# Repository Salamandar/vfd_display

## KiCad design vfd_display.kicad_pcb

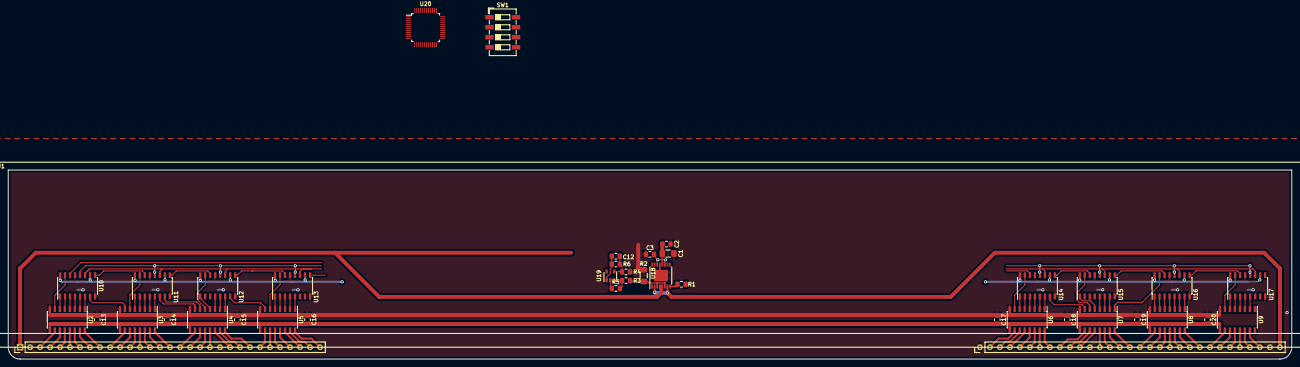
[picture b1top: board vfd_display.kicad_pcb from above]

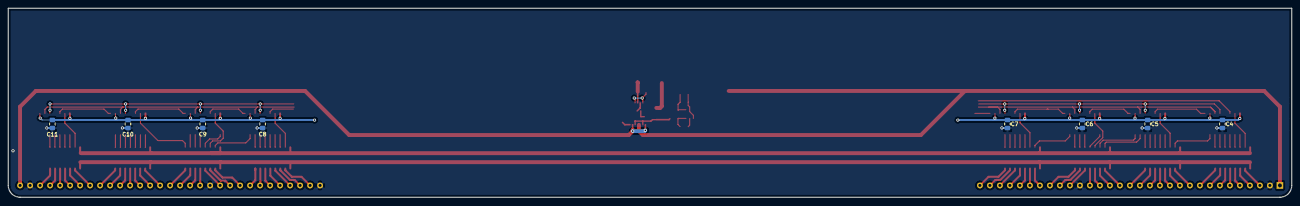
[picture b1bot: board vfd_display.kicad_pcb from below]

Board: 2 copper layers, 326.0 x 48.0 mm, 47 parts (8 on the bottom side), 132 nets.

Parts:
C1: 10u; C_1206_3216Metric_Pad1.42x1.75mm_HandSolder
C2, C4, C5, C6, C7, C8, C9, C10, C11, C13, C14, C15, C16, C17, C18, C19, C20: 100n; C_0805_2012Metric_Pad1.15x1.40mm_HandSolder
C3: 2.2u; C_0805_2012Metric_Pad1.15x1.40mm_HandSolder
C12: 33n; C_0805_2012Metric_Pad1.15x1.40mm_HandSolder
R1: 10k; R_0805_2012Metric_Pad1.15x1.40mm_HandSolder
R2: R_sense 500mW; R_1206_3216Metric_Pad1.42x1.75mm_HandSolder
R3, R4: 100; R_0805_2012Metric_Pad1.15x1.40mm_HandSolder
R5, R6: 47k; R_0805_2012Metric_Pad1.15x1.40mm_HandSolder
SW1: SW_DIP_x04; SW_DIP_SPSTx04_Slide_6.7x11.72mm_W6.73mm_P2.54mm_LowProfile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
U1: DC201LA
U2, U3, U4, U5, U6, U7, U8, U9: ULN2003; SOIC-16_3.9x9.9mm_P1.27mm
U10, U11, U12, U13, U14, U15, U16, U17: 74HC595; SOIC-16_3.9x9.9mm_P1.27mm
U18: DRV8848; TSSOP-16-1EP_4.4x5mm_P0.65mm
U19: TSZ121ILT; SOT-23-5
U20: STM32F302C8Tx; LQFP-48_7x7mm_P0.5mm

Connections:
+3V3: C4.1, C5.1, C6.1, C7.1, C8.1, C9.1, C10.1, C11.1, R1.2, U10.10, U10.16, U11.10, U11.16, U12.10, U12.16, U13.10, U13.16, U14.10, U14.16, U15.10, U15.16, U16.10, U16.16, U17.10, U17.16, U19.5, U20.9
/Filament_ADC: C12.1, R6.1, U19.1
/Filament_PWR: C1.2, C2.2, U18.12
/Grids_Anodes_Power: C13.2, C14.2, C15.2, C16.2, C17.2, C18.2, C19.2, C20.2, U2.9, U3.9, U4.9, U5.9, U6.9, U7.9, U8.9, U9.9
/VFD/Filament_In_A: U1.62, U18.2, U18.7
/VFD/Filament_In_B: U1.1, U18.4, U18.5
/VFD/G1: U7.5, U15.1
/VFD/G2: U7.6, U15.15
/VFD/G3: U7.7, U14.7
/VFD/G4: U6.1, U14.6
/VFD/G5: U6.2, U14.5
/VFD/G6: U6.3, U14.4
/VFD/G7: U6.4, U14.3
/VFD/G8: U6.5, U14.2
/VFD/G9: U6.6, U14.1
/VFD/G10: U6.7, U14.15
/VFD/G11: U5.1, U13.5
/VFD/G12: U5.2, U13.4
/VFD/G13: U5.3, U13.3
/VFD/G14: U5.4, U13.2
/VFD/G15: U5.5, U13.1
/VFD/G16: U5.6, U13.15
/VFD/G17: U5.7, U12.7
/VFD/G18: U4.1, U12.6
/VFD/G19: U4.2, U12.5
/VFD/G20: U4.3, U12.4
/VFD/P1: U2.7, U10.15
/VFD/P2: U2.6, U10.1
/VFD/P3: U2.5, U10.2
/VFD/P4: U2.4, U10.3
/VFD/P5: U2.3, U10.4
/VFD/P6: U2.2, U10.5
/VFD/P7: U2.1, U10.6
/VFD/P8: U3.7, U10.7
/VFD/P9: U3.6, U11.15
/VFD/P10: U3.5, U11.1
/VFD/P11: U3.4, U11.2
/VFD/P12: U3.3, U11.3
/VFD/P13: U3.2, U11.4
/VFD/P14: U3.1, U11.5
/VFD/P15: U4.7, U11.6
/VFD/P16: U4.6, U11.7
/VFD/P17: U4.5, U12.15
/VFD/P18: U4.4, U12.1
/VFD/P19: U9.2, U17.5
/VFD/P20: U9.3, U17.4
/VFD/P21: U9.4, U17.3
/VFD/P22: U9.5, U17.2
/VFD/P23: U9.6, U17.1
/VFD/P24: U9.7, U17.15
/VFD/P25: U8.1, U16.7
/VFD/P26: U8.2, U16.6
/VFD/P27: U8.3, U16.5
/VFD/P28: U8.4, U16.4
/VFD/P29: U8.5, U16.3
/VFD/P30: U8.6, U16.2
/VFD/P31: U8.7, U16.1
/VFD/P32: U7.1, U16.15
/VFD/P33: U7.2, U15.7
/VFD/P34: U7.3, U15.6
/VFD/P35: U7.4, U15.5
/VFD/RCLK1: U10.12, U11.12, U12.12, U13.12
/VFD/RCLK2: U14.12, U15.12, U16.12, U17.12
/VFD/SRCLK1: U10.11, U11.11, U12.11, U13.11
/VFD/SRCLK2: U14.11, U15.11, U16.11, U17.11
GND: C1.1, C2.1, C3.1, C4.2, C5.2, C6.2, C7.2, C8.2, C9.2, C10.2, C11.2, C13.1, C14.1, C15.1, C16.1, C17.1, C18.1, C19.1, C20.1, R2.2, R4.2, R5.1, SW1.5, SW1.6, SW1.7, SW1.8, U1.2, U1.21, U1.32, U1.43, U1.61, U2.8, U3.8, U4.8, U5.8, U6.8, U7.8, U8.8, U9.8, U10.8, U10.13, U11.8, U11.13, U12.8, U12.13, U13.8, U13.13, U14.8, U14.13, U15.8, U15.13, U16.8, U16.13, U17.8, U17.13, U18.13, U18.17, U19.2, U20.8, U20.23, U20.35, U20.47
unnamed: C3.2, U18.11, U18.14
unnamed: C12.2, R4.1, R6.2, U19.4
unnamed: R1.1, U18.8
unnamed: R2.1, R3.2, U18.3, U18.6
unnamed: R3.1, R5.2, U19.3
unnamed: U1.3, U2.10
unnamed: U1.4, U2.11
unnamed: U1.5, U2.12
unnamed: U1.6, U2.13
unnamed: U1.7, U2.14
unnamed: U1.8, U2.15
unnamed: U1.9, U2.16
unnamed: U1.10, U3.10
unnamed: U1.11, U3.11
unnamed: U1.12, U3.12
unnamed: U1.13, U3.13
unnamed: U1.14, U3.14
unnamed: U1.15, U3.15
unnamed: U1.16, U3.16
unnamed: U1.17, U4.10
unnamed: U1.18, U4.11
unnamed: U1.19, U4.12
unnamed: U1.20, U4.13
unnamed: U1.22, U4.14
unnamed: U1.23, U4.15
unnamed: U1.24, U4.16
unnamed: U1.25, U5.10
unnamed: U1.26, U5.11
unnamed: U1.27, U5.12
unnamed: U1.28, U5.13
unnamed: U1.29, U5.14
unnamed: U1.30, U5.15
unnamed: U1.31, U5.16
unnamed: U1.33, U6.10
unnamed: U1.34, U6.11
unnamed: U1.35, U6.12
unnamed: U1.36, U6.13
unnamed: U1.37, U6.14
unnamed: U1.38, U6.15
unnamed: U1.39, U6.16
unnamed: U1.40, U7.10
unnamed: U1.41, U7.11
unnamed: U1.42, U7.12
unnamed: U1.44, U7.13
unnamed: U1.45, U7.14
unnamed: U1.46, U7.15
unnamed: U1.47, U7.16
unnamed: U1.48, U8.10
unnamed: U1.49, U8.11
unnamed: U1.50, U8.12
unnamed: U1.51, U8.13
unnamed: U1.52, U8.14
unnamed: U1.53, U8.15
unnamed: U1.54, U8.16
unnamed: U1.55, U9.10
unnamed: U1.56, U9.11
unnamed: U1.57, U9.12
unnamed: U1.58, U9.13
unnamed: U1.59, U9.14
unnamed: U1.60, U9.15
unnamed: U10.9, U11.14
unnamed: U11.9, U12.14
unnamed: U12.9, U13.14
unnamed: U14.9, U15.14
unnamed: U15.9, U16.14
unnamed: U16.9, U17.14

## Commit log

2018-11-26 add files raw
2018-12-07 cleanup electronics
2018-12-07 add .gitignore
2019-02-21 routage terminé
2019-02-21 Fix shift registers outputs. Add text description files
2019-02-21 remove global labels
2019-02-21 reroute a bit
2019-02-21 refactoring
2019-06-07 continue circuitry
2020-02-28 todo
2022-01-04 Move sources
2022-01-04 Bump to Kicad 6!
